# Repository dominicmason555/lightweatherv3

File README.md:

# Light Weather V3

I made a temperature/pressure/humidity/gas sensor and general I/O interface for
my "smart flat".

[Full write-up](https://domson.dev/projects/lightweather.html) of versions 1
through 3 (this version) on my [personal website](https://domson.dev).

It features an ESP32-C3 controlling two NMOS outputs, one current-limited USB A
(power only) output, and an addressable RGB LED. It has pressure, temperature,
humidity, and gas sensors, and an IR receiver. These can be controlled using
MQTT over WiFi, or using an IR remote.

- [Schematic](./pictures/lightweather_schematic.pdf)
- [Firmware](./firmware/)

The hardware and firmware are open-source, the firmware (everything in
the [firmware](./firmware/) directory) is licensed under the
[GPL V3](./firmware/LICENSE).
The hardware (everything else) is licensed under the
[CERN Open Hardware Licence Version 2 - Strongly Reciprocal](./LICENSE).
The general gist is that if you feel like using or modifying anything here,
good luck, have fun, and publish what you make as open-source too.

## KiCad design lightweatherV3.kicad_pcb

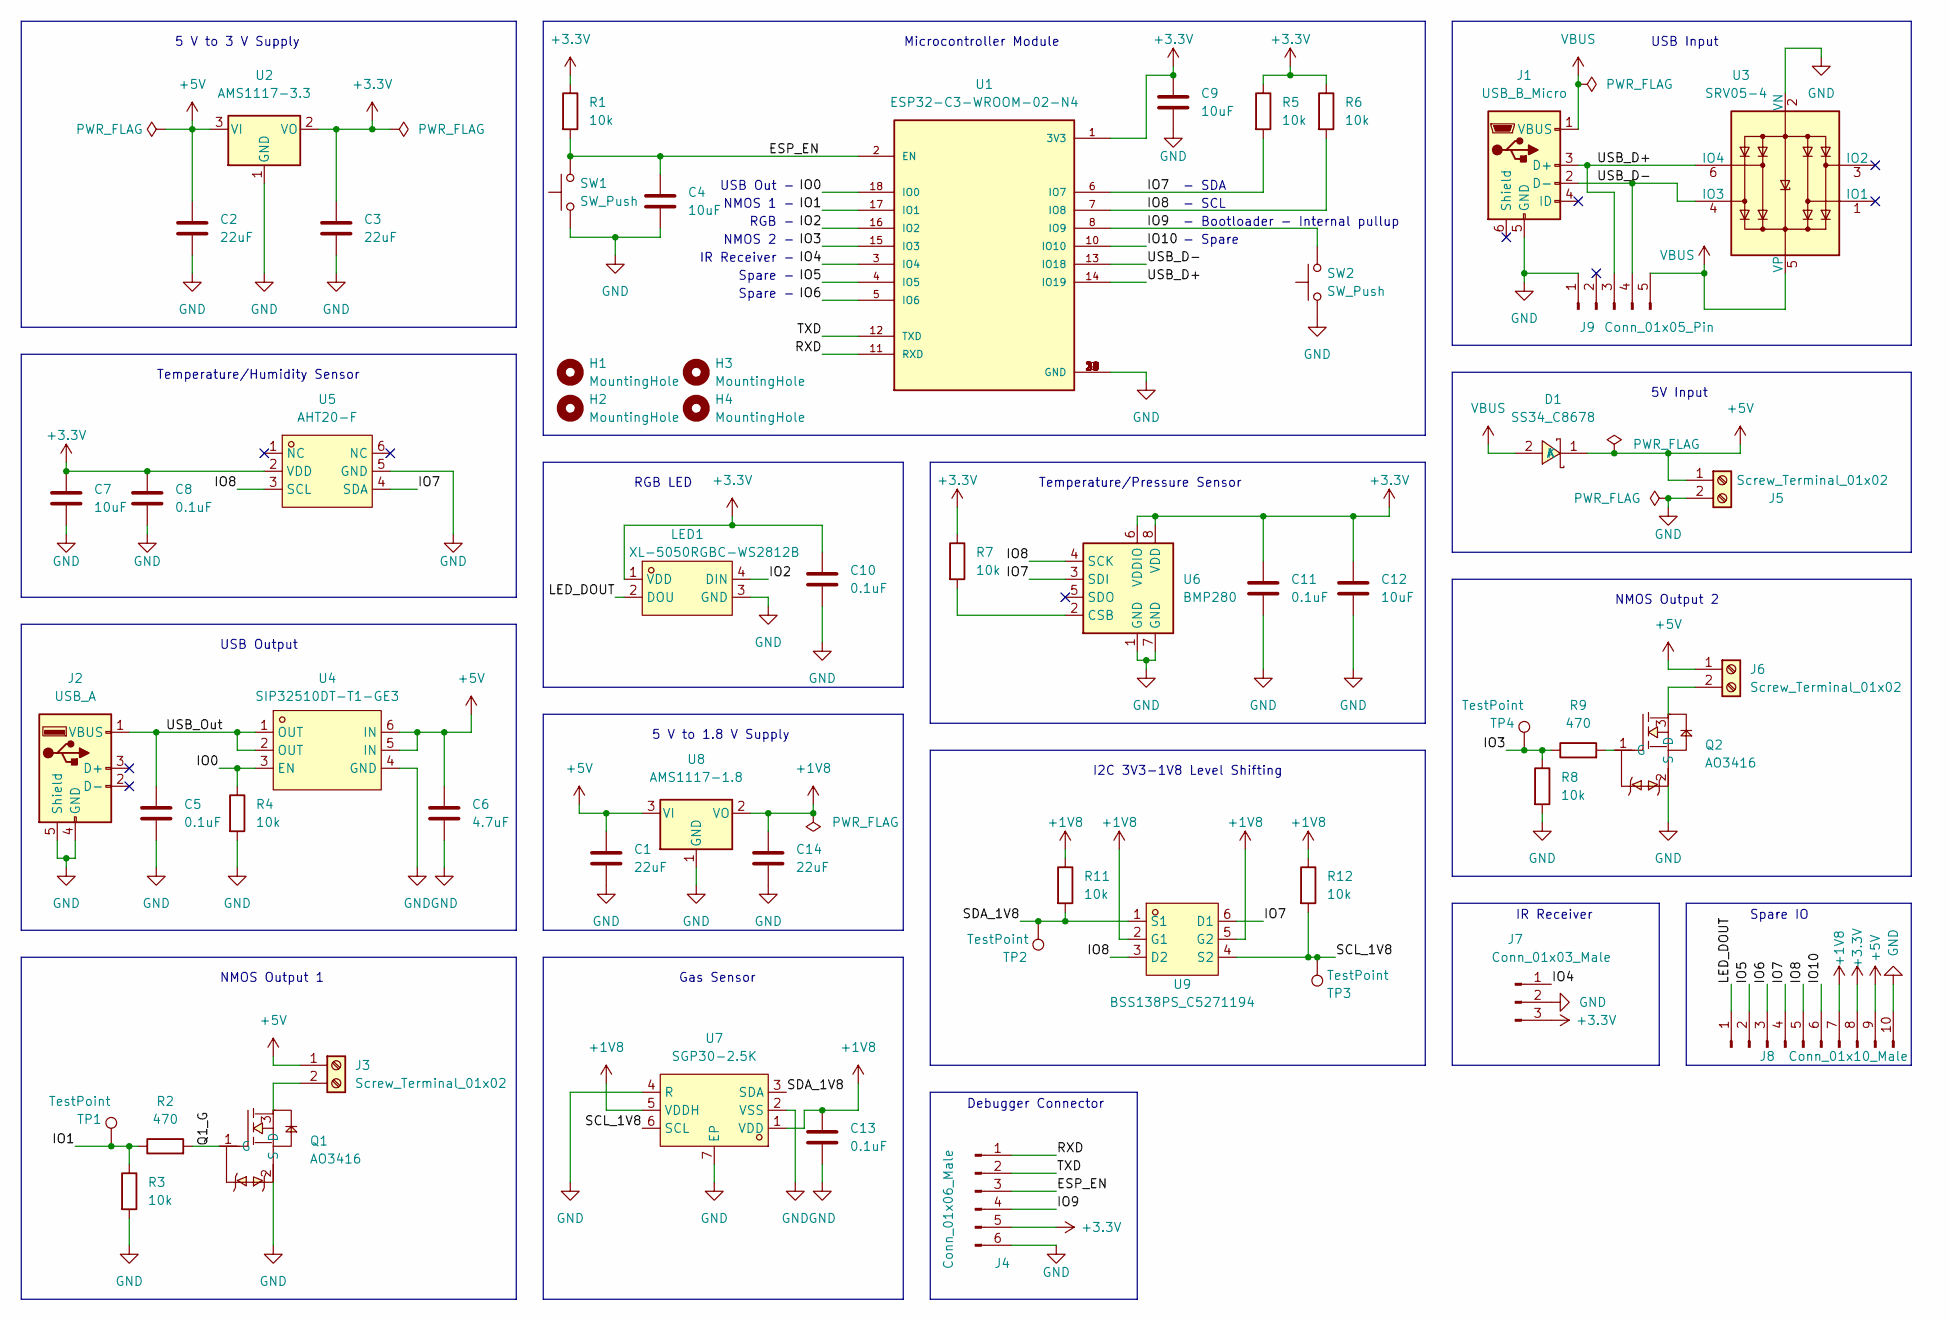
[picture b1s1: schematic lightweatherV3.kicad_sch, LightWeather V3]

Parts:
C1, C2, C3, C14: 22uF; C_0805_2012Metric_Pad1.18x1.45mm_HandSolder
C4, C7, C9, C12: 10uF; C_0805_2012Metric_Pad1.18x1.45mm_HandSolder
C5, C8, C10, C11, C13: 0.1uF; C_0805_2012Metric_Pad1.18x1.45mm_HandSolder
C6: 4.7uF; C_0805_2012Metric_Pad1.18x1.45mm_HandSolder
D1: SS34_C8678; SMA_L4.3-W2.6-LS5.2-RD; LCSC Part C8678
H1, H2, H3, H4: MountingHole; MountingHole_3.2mm_M3
J1: USB_B_Micro; MICRO-USB-SMD_U254-051T-4BH83-S1S
J2: USB_A; USB_A_Molex_67643_Horizontal
J3, J5, J6: Screw_Terminal_01x02; TerminalBlock_Altech_AK300-2_P5.00mm
J4: Conn_01x06_Male; PinHeader_1x06_P2.54mm_Vertical
J7: Conn_01x03_Male; PinHeader_1x03_P2.54mm_Vertical
J8: Conn_01x10_Male; PinHeader_1x10_P2.54mm_Vertical
J9: Conn_01x05_Pin; PinHeader_1x05_P2.54mm_Vertical
LED1: XL-5050RGBC-WS2812B; LED-SMD_4P-L5.0-W5.0-BL_XL-5050RGBC; LCSC Part C2843785
Q1, Q2: AO3416; SOT-23-3_L2.9-W1.6-P1.90-LS2.8-BR; LCSC Part C43307
R1, R3, R4, R5, R6, R7, R8, R11, R12: 10k; R_0805_2012Metric_Pad1.20x1.40mm_HandSolder
R2, R9: 470; R_0805_2012Metric_Pad1.20x1.40mm_HandSolder
SW1, SW2: SW_Push; SW_PUSH_6mm
TP1, TP2, TP3, TP4: TestPoint; TestPoint_Pad_D2.0mm
U1: ESP32-C3-WROOM-02-N4; MODULE_ESP32-C3-WROOM-02-H4
U2: AMS1117-3.3; SOT-223-3_TabPin2
U3: SRV05-4; SOT-23-6
U4: SIP32510DT-T1-GE3; SOT-23-6_L2.9-W1.6-P0.95-LS2.8-BR; LCSC Part C145264
U5: AHT20-F; SENSOR-SMD-6_AHT20; LCSC Part C3012622
U6: BMP280; Bosch_LGA-8_2x2.5mm_P0.65mm_ClockwisePinNumbering
U7: SGP30-2.5K; DFN-6_L2.5-W2.5-P0.8-BL-EP; LCSC Part C514454
U8: AMS1117-1.8; SOT-223-3_TabPin2
U9: BSS138PS_C5271194; SOT-23-6_L2.9-W1.6-P0.95-LS2.8-BR; LCSC Part C5271194

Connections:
+1V8: C13.1, C14.1, J8.7, R11.1, R12.1, U7.1 (VDD), U7.5 (VDDH), U8.2 (VO), U9.2 (G1), U9.5 (G2)
+3.3V: C3.1, C7.1, C8.1, C9.1, C10.1, C11.1, C12.1, J4.5, J7.3, J8.8, LED1.1 (VDD), R1.1, R5.1, R6.1, R7.1, U1.1 (3V3), U2.2 (VO), U5.2 (VDD), U6.6 (VDDIO), U6.8 (VDD)
+5V: C1.1, C2.1, C6.1, D1.1 (K), J3.1, J5.1, J6.1, J8.9, U2.3 (VI), U4.5 (IN), U4.6 (IN), U8.3 (VI)
/ESP_EN: C4.1, J4.3, R1.2, SW1.2, U1.2 (EN)
/IO0: R4.1, U1.18 (IO0), U4.3 (EN)
/IO1: R2.1, R3.1, TP1.1, U1.17 (IO1)
/IO2: LED1.4 (DIN), U1.16 (IO2)
/IO3: R8.1, R9.1, TP4.1, U1.15 (IO3)
/IO4: J7.1, U1.3 (IO4)
/IO5: J8.2, U1.4 (IO5)
/IO6: J8.3, U1.5 (IO6)
/IO7: J8.4, R5.2, U1.6 (IO7), U5.4 (SDA), U6.3 (SDI), U9.6 (D1)
/IO8: J8.5, R6.2, U1.7 (IO8), U5.3 (SCL), U6.4 (SCK), U9.3 (D2)
/IO9: J4.4, SW2.2, U1.8 (IO9)
/IO10: J8.6, U1.10 (IO10)
/LED_DOUT: J8.1, LED1.2 (DOU)
/Q1_G: Q1.1 (G), R2.2
/RXD: J4.1, U1.11 (RXD)
/SCL_1V8: R12.2, TP3.1, U7.6 (SCL), U9.4 (S2)
/SDA_1V8: R11.2, TP2.1, U7.3 (SDA), U9.1 (S1)
/TXD: J4.2, U1.12 (TXD)
/USB_D+: J1.3 (D+), J9.3, U1.14 (IO19), U3.6 (IO4)
/USB_D-: J1.2 (D-), J9.4, U1.13 (IO18), U3.4 (IO3)
/USB_Out: C5.1, J2.1 (VBUS), U4.1 (OUT), U4.2 (OUT)
GND: C1.2, C2.2, C3.2, C4.2, C5.2, C6.2, C7.2, C8.2, C9.2, C10.2, C11.2, C12.2, C13.2, C14.2, J1.5 (GND), J2.4 (GND), J2.5 (Shield), J4.6, J5.2, J7.2, J8.10, J9.1, LED1.3 (GND), Q1.2 (S), Q2.2 (S), R3.2, R4.2, R8.2, SW1.1, SW2.1, U1.9 (GND), U1.19 (GND), U1.20 (GND), U1.21 (GND), U1.22 (GND), U1.23 (GND), U1.24 (GND), U1.25 (GND), U1.26 (GND), U1.27 (GND), U1.28 (GND), U1.29 (GND), U1.30 (GND), U1.31 (GND), U1.32 (GND), U1.33 (GND), U1.34 (GND), U1.35 (GND), U1.36 (GND), U1.37 (GND), U1.38 (GND), U1.39 (GND), U2.1 (GND), U3.2 (VN), U4.4 (GND), U5.5 (GND), U6.1 (GND), U6.7 (GND), U7.2 (VSS), U7.4 (R), U7.7 (EP), U8.1 (GND)
unnamed: J3.2, Q1.3 (D)
unnamed: J6.2, Q2.3 (D)
unnamed: Q2.1 (G), R9.2
unnamed: R7.2, U6.2 (CSB)
VBUS: D1.2 (A), J1.1 (VBUS), J9.5, U3.5 (VP)

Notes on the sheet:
- Bootloader - Internal pullup
- SDA
Spare IO
5 V to 1.8 V Supply
NMOS Output 1
Debugger Connector
- SCL
NMOS Output 2
5V Input
NMOS 1 -
USB Input
5 V to 3 V Supply
USB Out -
RGB LED
IR Receiver -
Temperature/Humidity Sensor
NMOS 2 -
IR Receiver
I2C 3V3-1V8 Level Shifting
Microcontroller Module
Temperature/Pressure Sensor
Spare -
Gas Sensor
RGB -
- Spare
USB Output

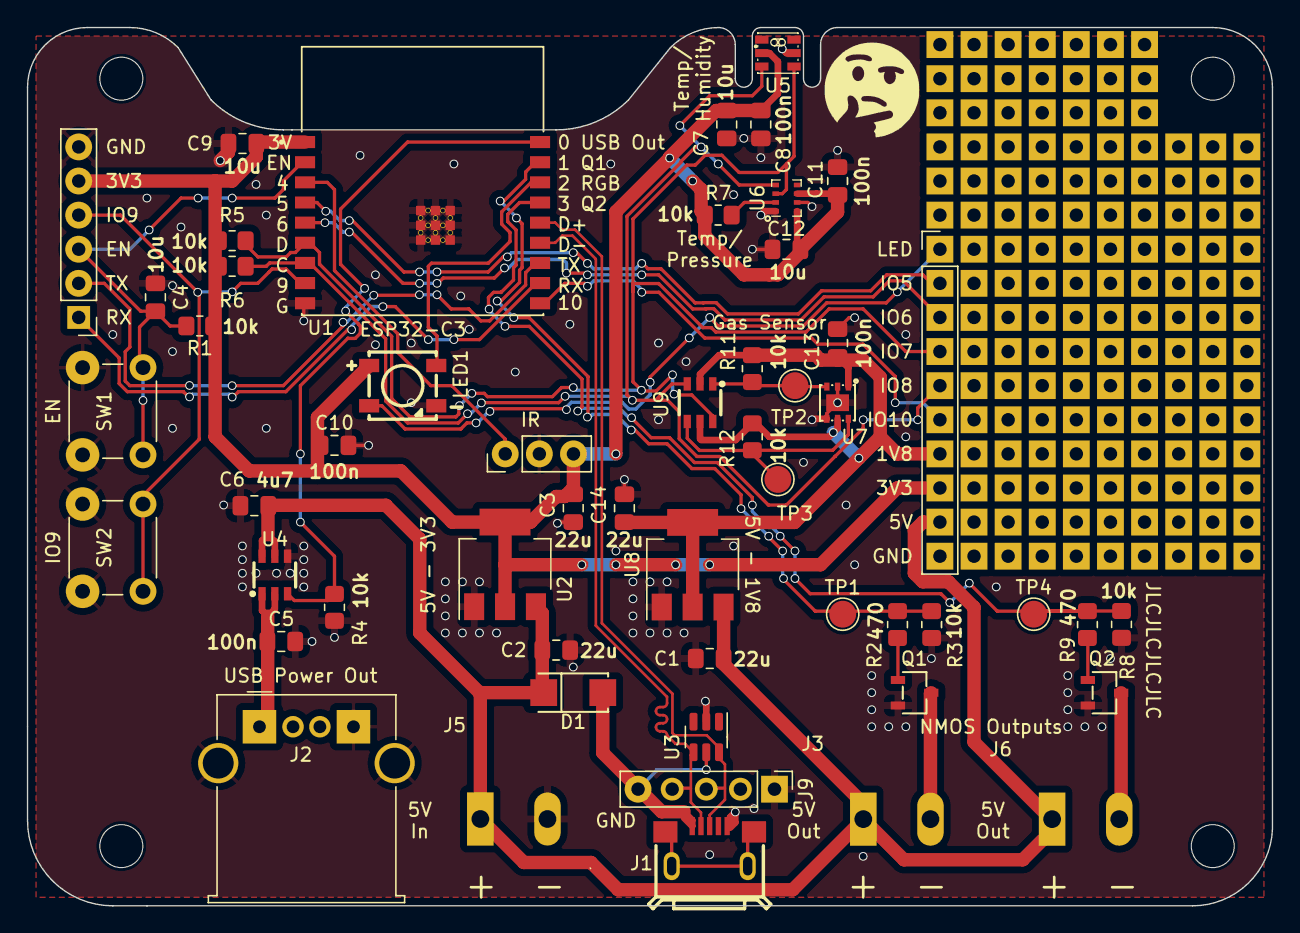
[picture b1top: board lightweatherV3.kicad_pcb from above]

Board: 2 copper layers, 92.7 x 65.4 mm, 57 parts (0 on the bottom side), 30 nets.

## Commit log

2024-09-10 Initial
2024-09-10 Added README and firmware
2024-09-10 Added license
2024-09-11 Typo
